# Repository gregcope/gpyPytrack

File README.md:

gpyPytrack
=========

Intro
==========
Based on a Pycom gpy (Bluetooth, WLAN, LTE) ESP32 MicroPython board and its associated Pytrack module that has a L76 GNSS module (and LIPO battery charger).  This project needs a Daughter board.

Aim
==========
* Be very, very low power (17uA when asleep with GNSS VBACKUP powered)
* Chargeable from 12-24V
* Rechargeable LIPO battery for easy parts sourcing
* Has a button to enable user wake up
* GNSS For location
* LTE for Coms
* BilgeSwitch and Temp (DS18B20) Alarms
* LED for Status (in switch)

Checks
=============
* Frequent
  * BilgeSwitch state
  * Temp above / below threshold
  * If in Alarm, send coms
* Less Frequent (less likely to change frequently)
  * Position
  * Battery volts
  * VCC volts
  * If in Alarm, send coms
* Daily
  * All of the above and sends status

Parts
==========
* [Pycom Gpy](https://pycom.io/hardware/gpy-specs)
* [Pycom pytrack](https://pycom.io/hardware/pytrack-specs/)
* [Mini Step Down Regulator Voltag Power Supply Module 4.5v~55v to 5v](https://www.ebay.co.uk/sch/i.html?_osacat=0&_odkw=Mini+Step+Down+Regulator+Voltag+Power+Supply+Module+4.5v~55v+to+5v&_from=R40&_trksid=p2334524.m570.l1313.TR0.TRC0.H0.XMini+Step+Down+Regulator+Voltag+Power+Supply+Module+4.5v~55v+to+5v+600ma.TRS0&_nkw=Mini+Step+Down+Regulator+Voltag+Power+Supply+Module+4.5v~55v+to+5v+600ma&_sacat=0)
* [DS18B20 Waterproof Digital Probe Temperature Sensor with Silicone Cable (higher temp) Thermometer](https://www.ebay.co.uk/sch/i.html?_from=R40&_trksid=p2380057.m570.l1313.TR0.TRC0.H0.Xvermont+l+tent.TRS0&_nkw=DS18B20+Waterproof+Digital+Probe+Temperature+Sensor+Silicone+Cable+Thermometer&_sacat=0)
* [12V 12mm LED Power Push Button Switch Momentary Waterproof Metal 4 Pin](https://www.ebay.co.uk/sch/i.html?_osacat=0&_odkw=waterproof+LED+switch+12mm&_from=R40&_trksid=p2334524.m570.l1313.TR0.TRC0.H0.Xwaterproof+LED+switch+12mm+momentary.TRS0&_nkw=waterproof+LED+switch+12mm+momentary&_sacat=0)
* 1200mah LIPO Battery
* Bilge Switch (any normally closed, simple switch would do)

Daughter board
==============
The Daughter board fits between the Gpy/Fipy and Pytrack module via headers (see pictures when I add them).  It is designed to hold certain parts and expose some pins via headers or JST connectors.   Its footprint is similar to the Pytrack to keep space requirements down.

The Daughter board mounts;
* VCC voltagedivider connected to an ADC pin to measure VCC
* Switchable Regulator with ENABLE pin connected to a pin
* JST(s) to breakout the relevant connections for the 11-36v VCC+GND, LED, Switch, DS18B20 Temp module, BilgeSwitch, 5V+GND for the Pytrack USB port
* __Note we will be putting 2x5pin XH JSTs on the Pytrack External IO to use those as well (simplifies this board and makes it smaller)__  

See the eagle files for the details.

Referances
=============
* https://blog.yavilevich.com/2017/03/efficient-dc-12v-to-5v-conversion-for-low-power-electronics-evaluation-of-six-modules/

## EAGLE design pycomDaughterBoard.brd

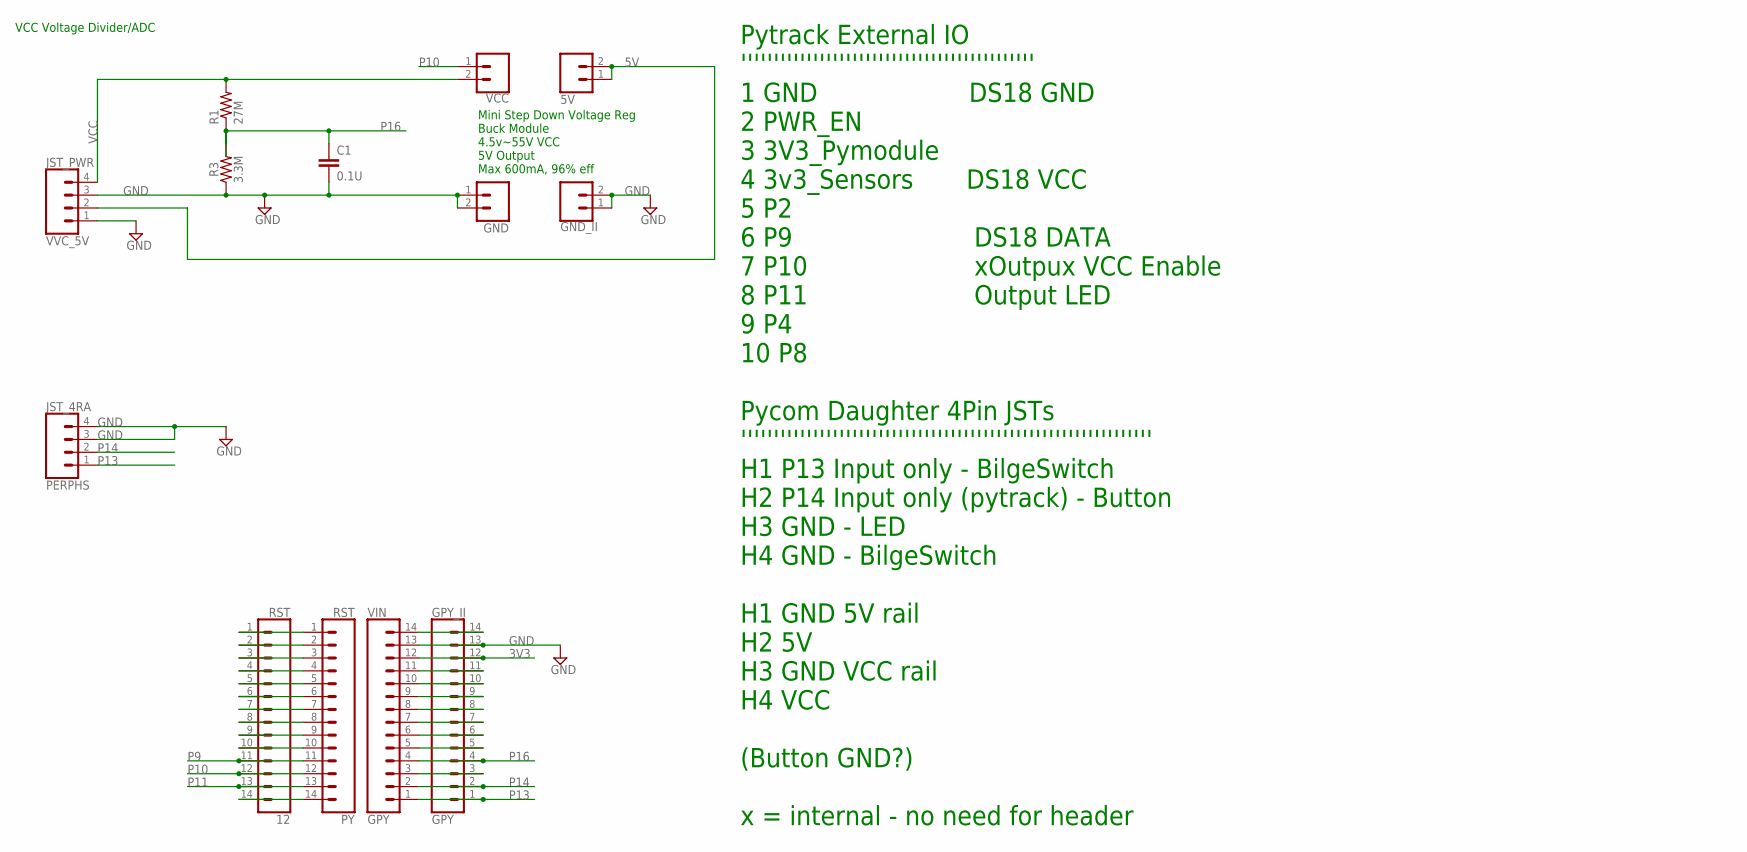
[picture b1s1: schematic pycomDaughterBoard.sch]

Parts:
5V: 5V; 1X02
12: RST; 1X14
C1: 0.1U; CAP-PTH-SMALL-KIT
GND: GND; 1X02
GND_II: GND; 1X02
GPY_II: GPY; 1X14
JST_4RA: PERPHS; JST-4-PTH
JST_PWR: VVC_5V; JST-4-PTH
PY: RST; 1X14
R1: 27M; 0309/12
R3: 3.3M; AXIAL-0.3
VCC: VCC; 1X02
VIN: GPY; 1X14

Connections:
3V3: GPY_II.12, VIN.12
5V: 5V.1, 5V.2, JST_PWR.2
GND: C1.2, GND.1, GND.2, GND_II.1, GND_II.2, GPY_II.13, JST_4RA.3, JST_4RA.4, JST_PWR.1, JST_PWR.3, R3.P$1 (1), VIN.13
unnamed: 12.1, PY.1
unnamed: 12.2, PY.2
unnamed: 12.3, PY.3
unnamed: 12.4, PY.4
unnamed: 12.5, PY.5
unnamed: 12.6, PY.6
unnamed: 12.7, PY.7
unnamed: 12.8, PY.8
unnamed: 12.9, PY.9
unnamed: GPY_II.14, VIN.14
unnamed: GPY_II.9, VIN.9
unnamed: 12.10, PY.10
unnamed: GPY_II.11, VIN.11
unnamed: GPY_II.10, VIN.10
unnamed: 12.14, PY.14
unnamed: GPY_II.8, VIN.8
unnamed: GPY_II.7, VIN.7
unnamed: GPY_II.3, VIN.3
P9: 12.11, PY.11
P10: 12.12, PY.12, VCC.1
P11: 12.13, PY.13
P13: GPY_II.1, JST_4RA.1, VIN.1
P14: GPY_II.2, JST_4RA.2, VIN.2
P16: C1.1, GPY_II.4, R1.1, R3.P$2 (2), VIN.4
P17: GPY_II.5, VIN.5
P18: GPY_II.6, VIN.6
VCC: JST_PWR.4, R1.2, VCC.2

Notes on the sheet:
VCC Voltage Divider/ADC
Mini Step Down Voltage Reg Buck Module 4.5v~55V VCC 5V Output Max 600mA, 96% eff
Pytrack External IO ''''''''''''''''''''''''''''''''''''''''''''' 1 GND DS18 GND 2 PWR_EN 3 3V3_Pymodule 4 3v3_Sensors DS18 VCC 5 P2 6 P9 DS18 DATA 7 P10 xOutpux VCC Enable 8 P11 Output LED 9 P4 10 P8 Pycom Daughter 4Pin JSTs ''''''''''''''''''''''''''''''''''''''''''''''''''''''''''''''' H1 P13 In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

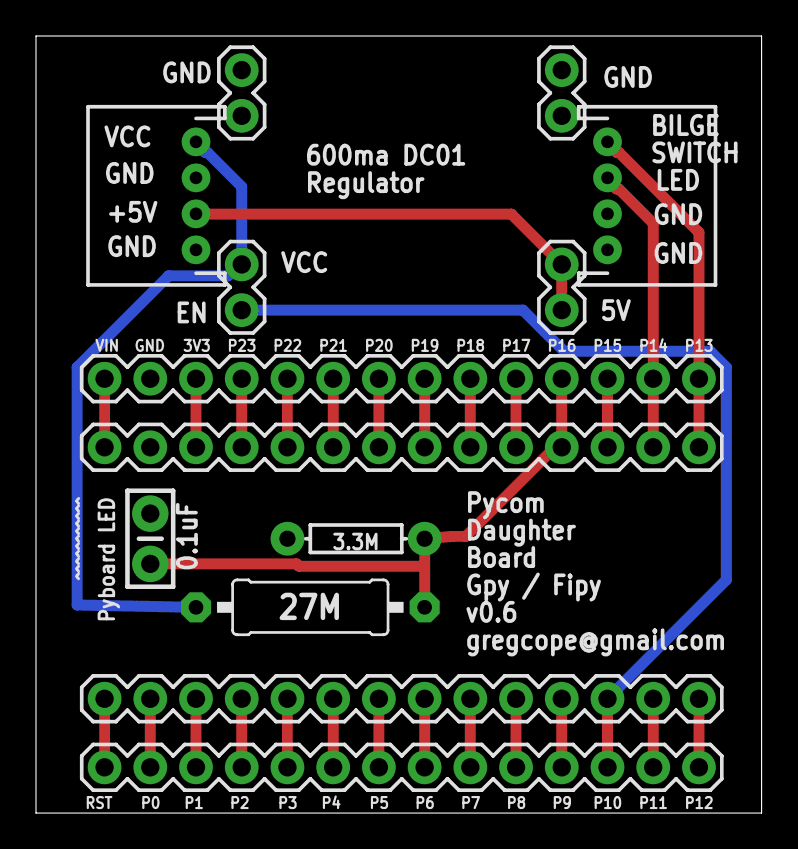
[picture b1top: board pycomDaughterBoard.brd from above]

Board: 2 copper layers, 40.3 x 43.2 mm, 13 parts (0 on the bottom side), 30 nets.

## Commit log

2018-02-25 initial comit
2018-02-25 readme
2018-02-25 Moved object to boot.py
2018-02-26 Typo+Correction
2018-02-26 added review of step down regs
2018-03-04 added parts
2018-03-04 added eagle v0.1 boards
2018-03-04 sunday rap up;
2018-03-05 adding board images
2018-03-05 list update
2018-03-05 list update1
2018-03-05 list updatew
2018-03-05 Correct list of checks
2018-03-05 Added class
2018-03-05 added classes
2018-03-05 added readme back
2018-03-05 added battery class
2018-03-05 added checks class
2018-03-05 Battery logic tested
2018-03-05 working out checks.
2018-03-05 added boot delay. Added logic for unset lastCheckTime
2018-03-06 Updated usage.
2018-03-06 Initial comit - boiler plate - does not actually work
2018-03-06 Added pins and more logic
2018-03-07 added BilgeSwitch class
2018-03-07 checks framework for bilgeSwitch
2018-03-07 added temp class
2018-03-07 temp check tested.
2018-03-07 added consts
2018-03-07 Added temp const, comments in checks
2018-03-08 added gps config, vin comments.
2018-03-11 Fixed Pins ...
2018-03-12 initial comit of a thing that tracks status
2018-03-12 er ... not sure why this needs a comit ...
2018-03-12 Initial stab...
2018-03-12 With GNS patch
2018-03-12 change a comment
2018-03-12 change to msec utime
2018-03-12 added link to NMEA doco
2018-03-14 Added const()
2018-03-14 Added VCCState.
2018-03-14 removed duff code from Copy&Paste of original.
2018-03-14 Changed to INTERVAL const
2018-03-14 Moved to INTERVAL const
2018-03-14 Initial comit.
2018-03-14 Case changes
2018-03-15 pin doco
2018-03-16 removed power pin as we are going to use 3V3_SENSORS on the pytrack
2018-03-16 changes to pin outs.
2018-03-17 Changed pins for Fipy and Gpy compatibility
2018-03-17 Rotation code
2018-03-17 Remove write comments
2018-03-17 debug print
2018-03-17 Debugging messages
2018-03-17 various logic fixes
2018-03-17 added method
2018-03-17 move code around.
2018-03-17 code tidy
2018-03-17 Changed to stateMachine
2018-03-17 changed to be generic
2018-03-30 typo change
2018-03-30 new v0.3 board
2018-03-30 Corrections / labels
2018-03-30 Added 5v
2018-03-30 Moved vias
2018-03-30 Aligned Pins with real board
2018-03-30 Text update, move VCC connector
2018-03-30 text update
2018-03-30 Setup Voltage divider and reg enable pin
2018-03-30 switch led on / off
2018-03-30 typo in examples
2018-03-30 switch objects round into list of might work vs still need some work
2018-03-31 Battery class looks like it should work, needs testing.
2018-03-31 Info on Daughter board + typos.
2018-03-31 added image
2018-03-31 Added code, TODO: async
2018-03-31 v0.4 of board, with JSR headers
2018-03-31 JST update
2018-03-31 Markdown fix.
2018-03-31 More doco
2018-04-01 Added VREF code
2018-04-01 SD card logic
2018-04-09 added comment
2018-04-09 Optimise config write
2018-04-15 Setup pins
2018-04-15 newline fix
2018-04-15 import right class!
2018-04-18 Board v0.6 updates
2018-04-18 updates to board layout/silkscreen 0.6v
2018-04-18 tweakette
2018-04-21 Doco updates
2018-04-22 Correction
2018-04-22 added some threading ideas
2018-04-22 Statemachine logic
2018-04-23 Temp threading
2018-04-23 added comments
2018-04-23 test

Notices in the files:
parts and their libraries:
SparkFun-Connectors: Licensing: Creative Commons ShareAlike 4.0 International - https://creativecommons.org/licenses/by-sa/4.0
